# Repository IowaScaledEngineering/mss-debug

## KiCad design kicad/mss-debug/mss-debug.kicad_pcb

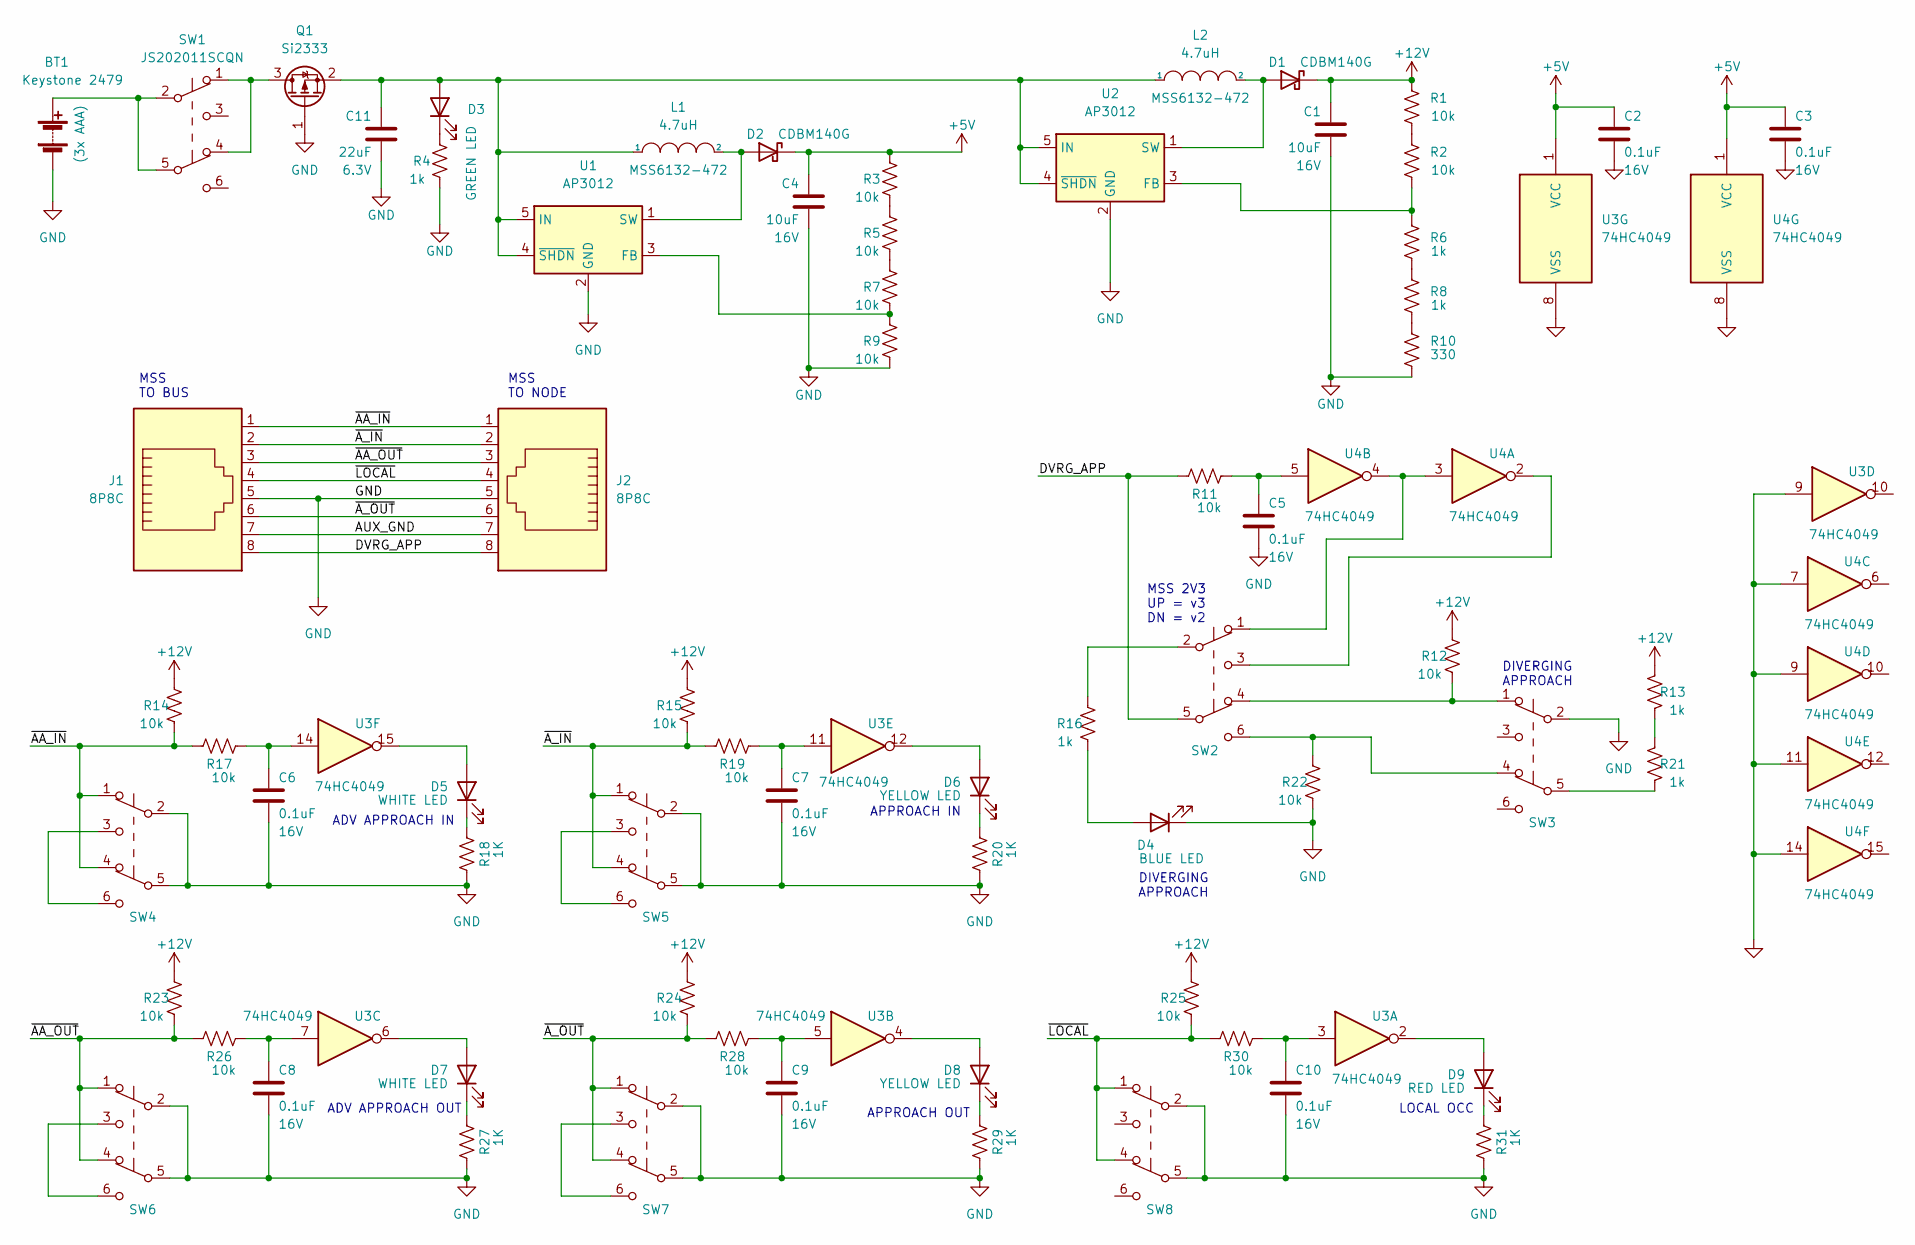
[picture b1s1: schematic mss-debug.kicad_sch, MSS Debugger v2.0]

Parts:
BT1: Keystone 2479; BatteryHolder_Keystone_2479_3xAAA
C1, C4: 10uF; C_0805_2012Metric; Voltage 16V
C2, C3, C5, C6, C7, C8, C9, C10: 0.1uF; C_0805_2012Metric; Voltage 16V
C11: 22uF; C_0805_2012Metric; Voltage 6.3V
D1, D2: CDBM140G; SOD-123T
D3: GREEN LED; LED_0805_2012Metric
D4: BLUE LED; LED_0805_2012Metric
D5, D7: WHITE LED; LED_0805_2012Metric
D6, D8: YELLOW LED; LED_0805_2012Metric
D9: RED LED; LED_0805_2012Metric
J1, J2: 8P8C; RJ45_Amphenol_54602-x08_Horizontal
L1, L2: 4.7uH; MSS6132-xxxMLC
Q1: Si2333; SOT-23
R1, R2, R3, R5, R7, R9, R11, R12, R14, R15, R17, R19, R22, R23, R24, R25, R26, R28, R30: 10k; R_0805_2012Metric
R4, R6, R8, R13, R16, R21: 1k; R_0805_2012Metric
R10: 330; R_0805_2012Metric
R18, R20, R27, R29, R31: 1K; R_0805_2012Metric
SW1, SW2, SW3, SW4, SW5, SW6, SW7, SW8: JS202011SCQN; SW_JS202011SCQN
U1, U2: AP3012; SOT-23-5
U3, U4: 74HC4049; SO-16_3.9x9.9mm_P1.27mm

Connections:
+5V: C2.1, C3.1, C4.1, D2.1 (K), R3.2, U3.1 (VCC), U4.1 (VCC)
+12V: C1.1, D1.1 (K), R1.2, R12.2, R13.2, R14.2, R15.2, R23.2, R24.2, R25.2
/AUX_GND: J1.7, J2.7
/DVRG_APP: J1.8, J2.8, R11.2, SW2.5 (B)
/~AA_IN: J1.1, J2.1, R14.1, R17.2, SW4.1 (A), SW4.4 (A); also elsewhere on the board
/~AA_OUT: J1.3, J2.3, R23.1, R26.2, SW6.1 (A), SW6.4 (A)
/~A_IN: J1.2, J2.2, R15.1, R19.2, SW5.1 (A), SW5.4 (A)
/~A_OUT: J1.6, J2.6, R24.1, R28.2, SW7.1 (A), SW7.4 (A)
/~LOCAL: J1.4, J2.4, R25.1, R30.2, SW8.1 (A), SW8.4 (A)
GND: BT1.2 (-), C1.2, C2.2, C3.2, C4.2, C5.2, C6.2, C7.2, C8.2, C9.2, C10.2, C11.2, D4.1 (K), J1.5, J2.5, Q1.1 (G), R4.1, R9.1, R10.1, R18.2, R20.2, R22.1, R27.2, R29.2, R31.2, SW3.2 (B), SW4.2 (B), SW4.5 (B), SW5.2 (B), SW5.5 (B), SW6.2 (B), SW6.5 (B), SW7.2 (B), SW7.5 (B), SW8.2 (B), SW8.5 (B), U1.2 (GND), U2.2 (GND), U3.8 (VSS), U3.9, U4.7, U4.8 (VSS), U4.9, U4.11, U4.14; also elsewhere on the board
unnamed: C5.1, R11.1, U4.5
unnamed: C6.1, R17.1, U3.14
unnamed: C7.1, R19.1, U3.11
unnamed: C8.1, R26.1, U3.7
unnamed: C9.1, R28.1, U3.5
unnamed: C10.1, R30.1, U3.3
unnamed: D3.1 (K), R4.2
unnamed: D4.2 (A), R16.1
unnamed: D5.2 (A), U3.15
unnamed: D6.2 (A), U3.12
unnamed: D7.2 (A), U3.6
unnamed: D8.2 (A), U3.4
unnamed: D9.1 (K), R31.1
unnamed: D9.2 (A), U3.2
unnamed: D1.2 (A), L2.2, U2.1 (SW)
unnamed: R1.1, R2.2
unnamed: R3.1, R5.2
unnamed: R5.1, R7.2
unnamed: R6.1, R8.2
unnamed: R8.1, R10.2
unnamed: R12.1, SW2.4 (A), SW3.1 (A)
unnamed: R13.1, R21.2
unnamed: R16.2, SW2.2 (B)
unnamed: D5.1 (K), R18.1
unnamed: D6.1 (K), R20.1
unnamed: R21.1, SW3.5 (B)
unnamed: R22.2, SW2.6 (C), SW3.4 (A)
unnamed: D7.1 (K), R27.1
unnamed: D8.1 (K), R29.1
unnamed: Q1.3 (D), SW1.1 (A), SW1.4 (A)
unnamed: BT1.1 (+), SW1.2 (B), SW1.5 (B)
unnamed: SW2.1 (A), U4.3, U4.4
unnamed: SW2.3 (C), U4.2
unnamed 43: SW4.3 (C), SW4.6 (C); also elsewhere on the board
unnamed: SW5.3 (C), SW5.6 (C)
unnamed: SW6.3 (C), SW6.6 (C)
unnamed: SW7.3 (C), SW7.6 (C)
unnamed: D2.2 (A), L1.2, U1.1 (SW)
unnamed: R7.1, R9.2, U1.3 (FB)
unnamed: C11.1, D3.2 (A), L1.1, L2.1, Q1.2 (S), U1.4 (~SHDN), U1.5 (IN), U2.4 (~SHDN), U2.5 (IN)
unnamed: R2.1, R6.2, U2.3 (FB)

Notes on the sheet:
MSS TO BUS
APPROACH IN
DIVERGING APPROACH
MSS TO NODE
ADV APPROACH OUT
APPROACH OUT
ADV APPROACH IN
LOCAL OCC
MSS 2V3 UP = v3 DN = v2

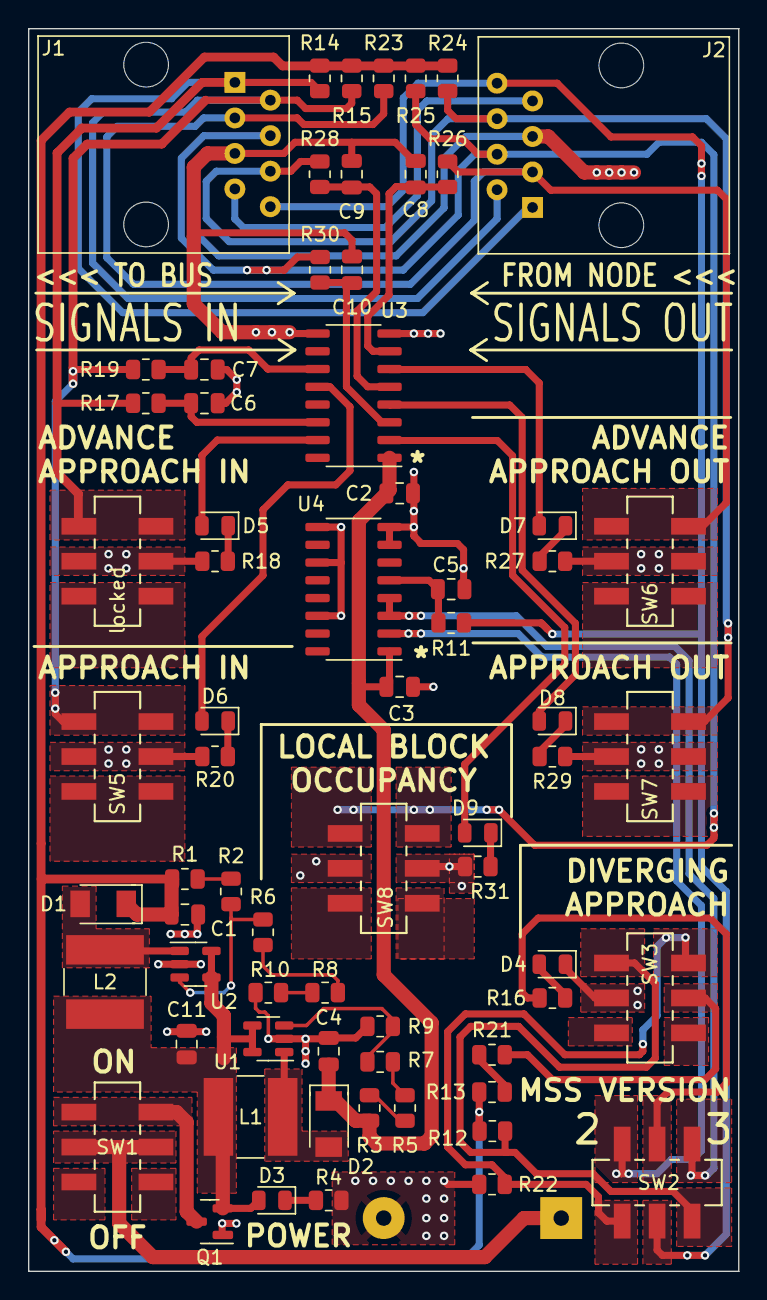
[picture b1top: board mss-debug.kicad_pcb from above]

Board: 2 copper layers, 50.8 x 88.9 mm, 69 parts (1 on the bottom side), 51 nets.

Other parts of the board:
locked: JS202011SCQN; SW_JS202011SCQN

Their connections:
/~AA_IN: locked.1 (A), locked.4 (A); also elsewhere on the board
GND: locked.2 (B), locked.5 (B); also elsewhere on the board
unnamed 43: locked.3 (C), locked.6 (C); also elsewhere on the board

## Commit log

2016-06-08 Initial version
2016-06-08 Add more copper around the switches for mechanical stability
2016-06-08 Added a bit more copper plane around the 5V regulator
2016-06-08 Add pg of 1.0
2016-09-27 Add PCB drawing and manual
2016-11-29 Fixed schematic
2017-06-15 Added bag top
2022-06-25 Update border on schematic so I didn't go blind trying to read it
2024-08-17 Start on v2 of the debug in kicad
2024-08-18 Initial cut of the 2.0 board
2024-08-18 Fix back text
2024-08-26 pg debug 2.0

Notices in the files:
kicad/mss-debug/mss-debug.kicad_pcb:
www.iascaled.com ©2024
